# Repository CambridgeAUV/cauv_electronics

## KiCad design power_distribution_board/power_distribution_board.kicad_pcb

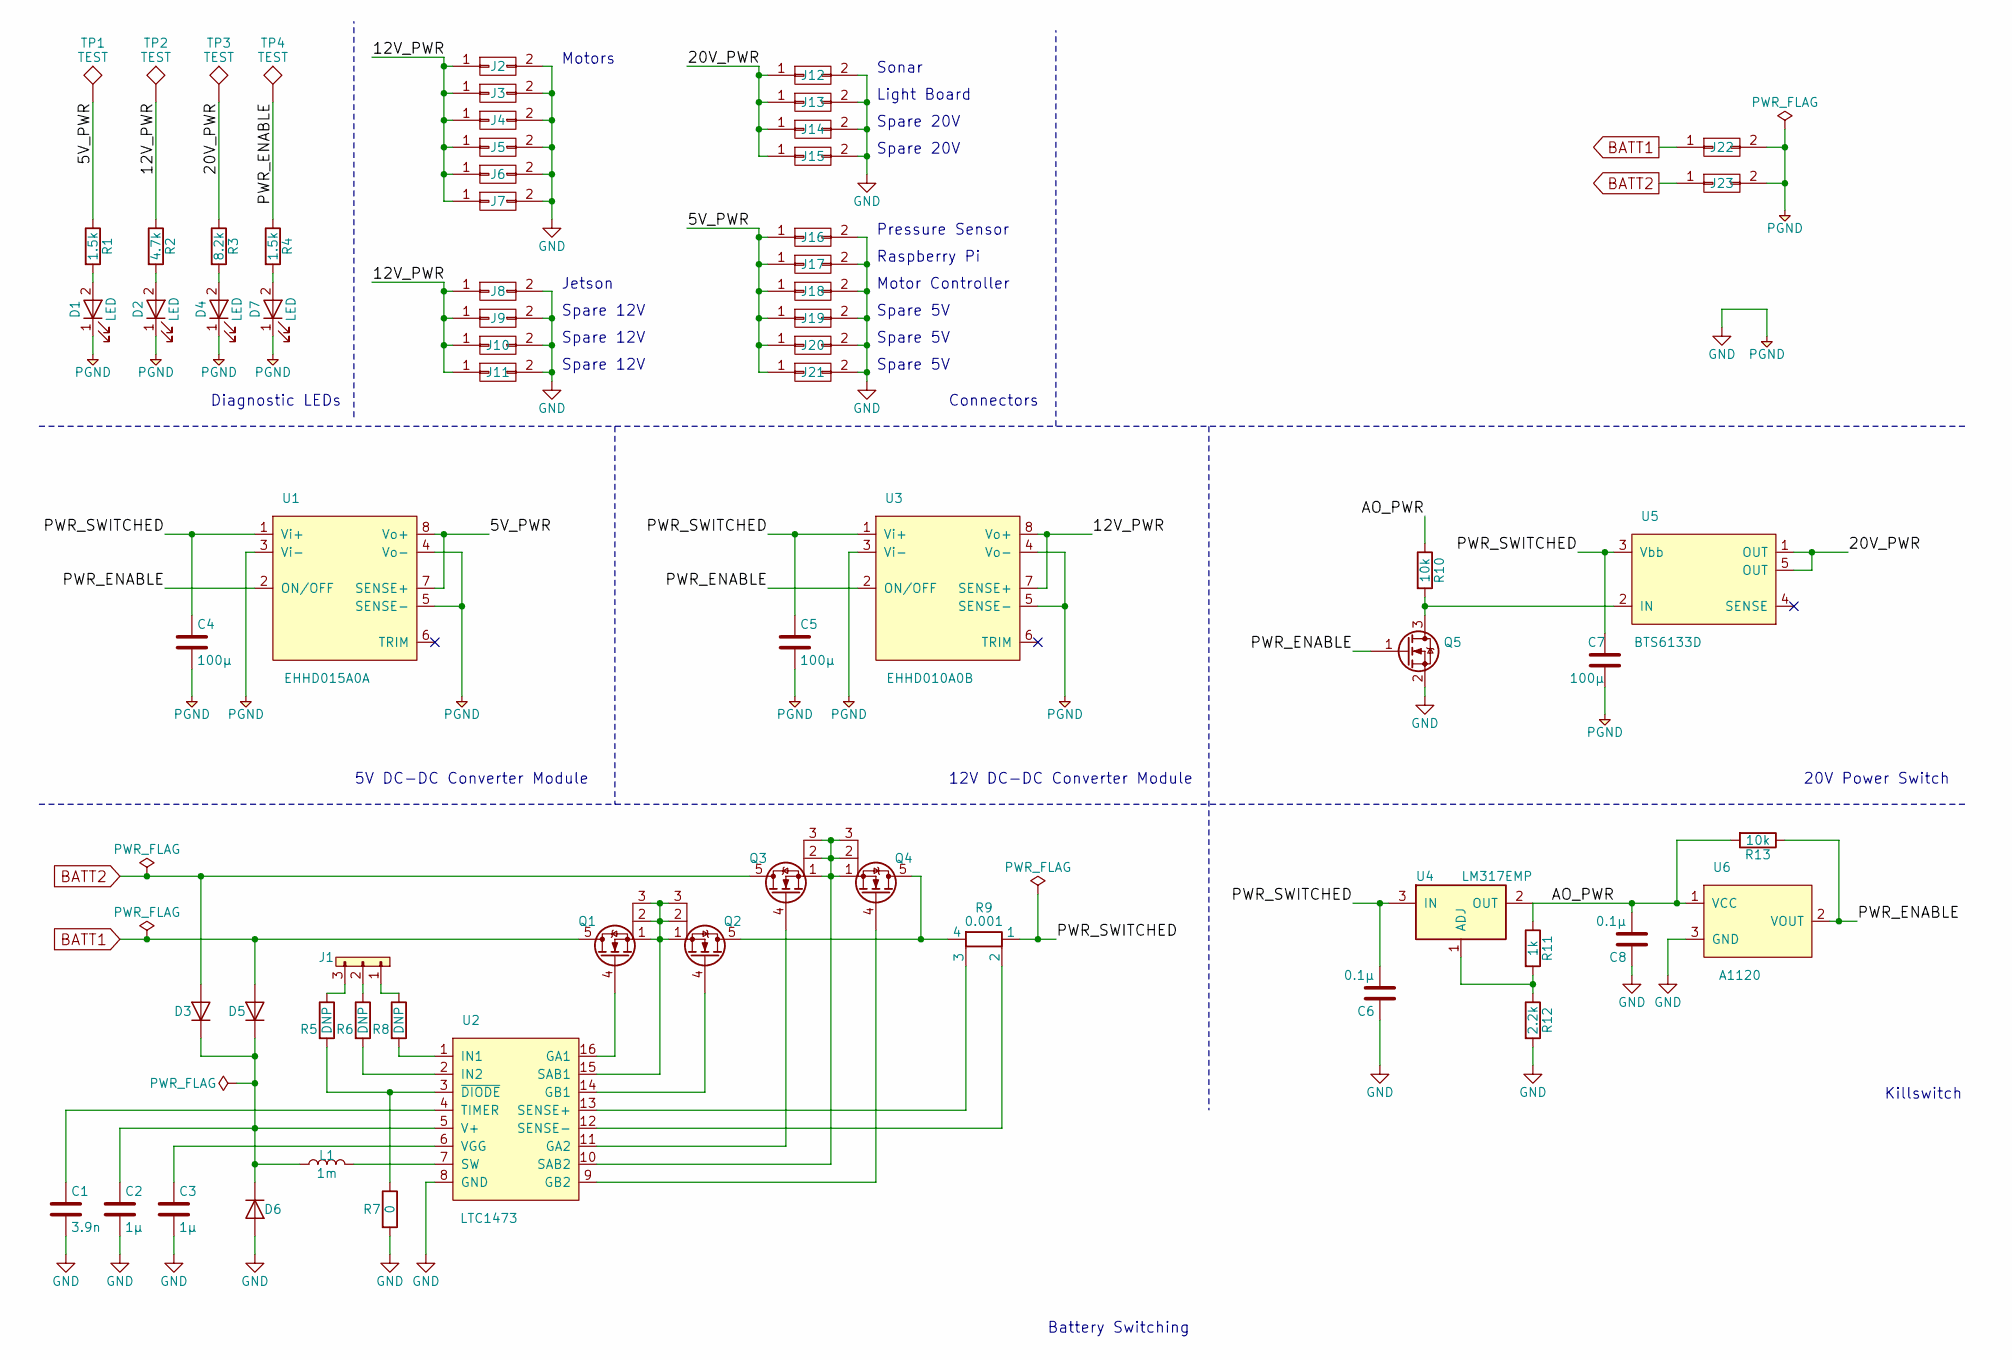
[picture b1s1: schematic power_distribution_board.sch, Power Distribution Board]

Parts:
C1: 3.9n; C_0603
C2, C3: 1μ; C_0603
C4, C5, C7: 100μ; C_1210
C6, C8: 0.1μ; C_0603
D1, D2, D4, D7: LED; LED_0805
D3, D5, D6: D; D_SMA
J1: CONN_01x03; Molex_KK-6410-03_03x2.54mm_Straight
J2, J3, J4, J5, J6, J7, J8, J9, J10, J11, J12, J13, J14, J15, J16, J17, J18, J19, J20, J21, J22, J23: CONN_02X01; Molex_MiniFit-JR-5556-02A_2x01x4.20mm_Straight
L1: 1m; L_1812
Q1, Q2, Q3, Q4: NMOS_SSSGD; SOT-669_LFPAK
Q5: Q_NMOS_GSD; SOT-23
R1, R4: 1.5k; R_0603
R2: 4.7k; R_0603
R3: 8.2k; R_0603
R5, R6, R8: DNP; R_0603
R7: 0; R_0603
R9: 0.001; WSLP2726
R10, R13: 10k; R_0603
R11: 1k; R_0603
R12: 2.2k; R_0603
TP1, TP2, TP3, TP4: TEST; TESTPAD
U1: EHHD015A0A
U2: LTC1473; SSOP-16_3.9x4.9mm_Pitch0.635mm
U3: EHHD010A0B; EHHD015A0A
U4: LM317EMP; SOT-223
U5: BTS6133D; TO-252-5_TabPin3
U6: A1120; Molex_KK-6410-03_03x2.54mm_Straight

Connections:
/5V_PWR: J16.1, J17.1, J18.1, J19.1, J20.1, J21.1, R1.1, TP1.1, U1.7 (SENSE+), U1.8 (Vo+)
/12V_PWR: J2.1, J3.1, J4.1, J5.1, J6.1, J7.1, J8.1, J9.1, J10.1, J11.1, R2.1, TP2.1, U3.7 (SENSE+), U3.8 (Vo+)
/20V_PWR: J12.1, J13.1, J14.1, J15.1, R3.1, TP3.1, U5.1 (OUT), U5.5 (OUT)
/AO_PWR: C8.2, R10.1, R11.1, R13.2, U4.2 (OUT), U6.1 (VCC)
/PWR_ENABLE: Q5.1 (G), R4.1, R13.1, TP4.1, U1.2 (ON/OFF), U3.2 (ON/OFF), U6.2 (VOUT)
/PWR_SWITCHED: C4.1, C5.1, C6.2, C7.1, R9.1, U1.1 (Vi+), U3.1 (Vi+), U4.3 (IN), U5.3 (Vbb)
BATT1: D5.2 (A), J22.1, Q1.5 (D)
BATT2: D3.2 (A), J23.1, Q3.5 (D)
GND: C1.2, C2.2, C3.2, C4.2, C5.2, C6.1, C7.2, C8.1, D1.1 (K), D2.1 (K), D4.1 (K), D6.2 (A), D7.1 (K), J2.2, J3.2, J4.2, J5.2, J6.2, J7.2, J8.2, J9.2, J10.2, J11.2, J12.2, J13.2, J14.2, J15.2, J16.2, J17.2, J18.2, J19.2, J20.2, J21.2, J22.2, J23.2, Q5.2 (S), R7.2, R12.2, U1.3 (Vi-), U1.4 (Vo-), U1.5 (SENSE-), U2.8 (GND), U3.3 (Vi-), U3.4 (Vo-), U3.5 (SENSE-), U6.3 (GND)
unnamed: C1.1, U2.4 (TIMER)
unnamed: C2.1, D3.1 (K), D5.1 (K), D6.1 (K), L1.1, U2.5 (V+)
unnamed: C3.1, U2.6 (VGG)
unnamed: D1.2 (A), R1.2
unnamed: D2.2 (A), R2.2
unnamed: D4.2 (A), R3.2
unnamed: D7.2 (A), R4.2
unnamed: J1.1, R8.1
unnamed: J1.2, R6.1
unnamed: J1.3, R5.1
unnamed: L1.2, U2.7 (SW)
unnamed: Q1.1 (S), Q1.2 (S), Q1.3 (S), Q2.1 (S), Q2.2 (S), Q2.3 (S), U2.15 (SAB1)
unnamed: Q1.4 (G), U2.16 (GA1)
unnamed: Q2.4 (G), U2.14 (GB1)
unnamed: Q2.5 (D), Q4.5 (D), R9.4
unnamed: Q3.1 (S), Q3.2 (S), Q3.3 (S), Q4.1 (S), Q4.2 (S), Q4.3 (S), U2.10 (SAB2)
unnamed: Q3.4 (G), U2.11 (GA2)
unnamed: Q4.4 (G), U2.9 (GB2)
unnamed: Q5.3 (D), R10.2, U5.2 (IN)
unnamed: R5.2, R7.1, U2.3 (~DIODE)
unnamed: R6.2, U2.2 (IN2)
unnamed: R8.2, U2.1 (IN1)
unnamed: R9.2, U2.12 (SENSE-)
unnamed: R9.3, U2.13 (SENSE+)
unnamed: R11.2, R12.1, U4.1 (ADJ)

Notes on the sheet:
Battery Switching
Killswitch
5V DC-DC Converter Module
12V DC-DC Converter Module
20V Power Switch
Diagnostic LEDs
Motors
Jetson
Spare 12V
Sonar
Light Board
Spare 20V
Pressure Sensor
Raspberry Pi
Motor Controller
Spare 5V
Connectors

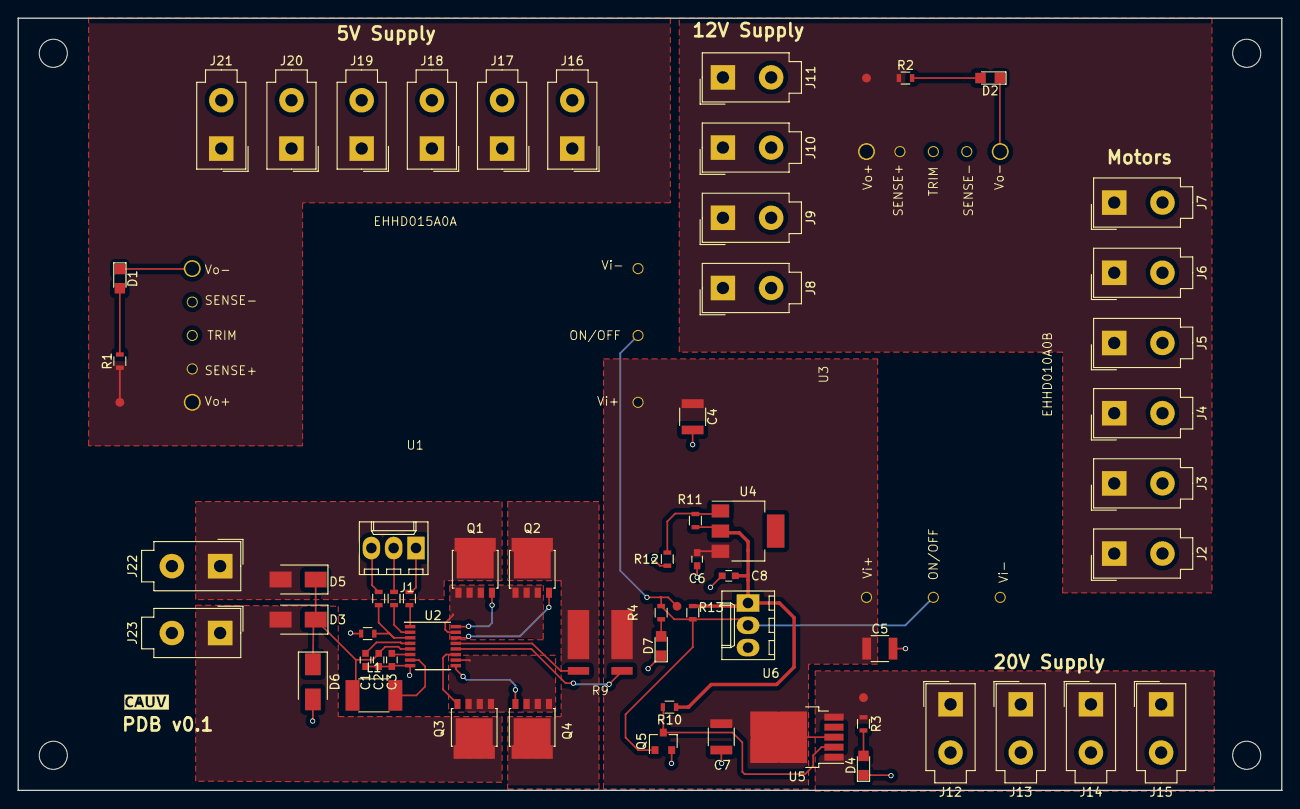
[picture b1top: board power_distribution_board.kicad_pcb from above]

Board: 2 copper layers, 144.0 x 88.0 mm, 67 parts (0 on the bottom side), 34 nets.

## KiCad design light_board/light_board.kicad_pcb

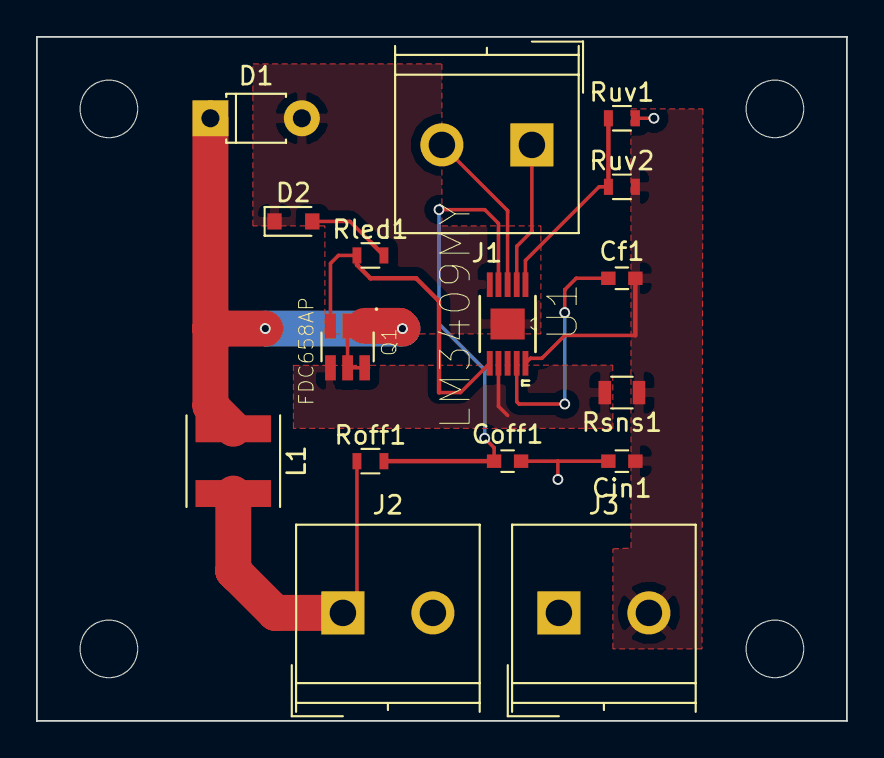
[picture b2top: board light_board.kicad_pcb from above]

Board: 2 copper layers, 45.0 x 38.0 mm, 16 parts (0 on the bottom side), 12 nets.

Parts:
Cf1: 1uF; C_0603
Cin1: 4u7F; C_0603
Coff1: 470pF; C_0603
D1: SCHOTTKY; D_T-1_P5.08mm_Horizontal
D2: Gate; D_0805
J1: PWM; TerminalBlock_Philmore_TB132_02x5mm_Straight
J2: Led; TerminalBlock_Philmore_TB132_02x5mm_Straight
J3: Power; TerminalBlock_Philmore_TB132_02x5mm_Straight
L1: 12.5uH; L_Taiyo-Yuden_MD-5050
Q1: FDC658AP; FDC658AP_FDC658AP
Rled1: 1kR; R_0603
Roff1: 12k; R_0603
Rsns1: 0.15R; R_0805
Ruv1: 6K49; R_0603
Ruv2: 73K2; R_0603
U1: LM3409MY; LM3409

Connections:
/COFF: Coff1.1, Roff1.2, U1.4
/CSN: Q1.4, Rsns1.2, U1.7
/CSP: Cf1.2, Cin1.1, J3.2, Rsns1.1, Ruv2.2, U1.8, U1.10
/LEDVcc: J2.1, L1.2, Roff1.1
/PGATE: Q1.3, Rled1.1, U1.6
/UVLO: Ruv1.1, Ruv2.1, U1.1
/diodeToLToPMOS: D1.1, L1.1, Q1.1, Q1.2, Q1.5, Q1.6
/inputSignal: J1.2, U1.3
/notUsed: J1.1, U1.2
GND: Cin1.2, Coff1.2, D1.2, D2.1, J2.2, J3.1, Ruv1.2, U1.5, U1.11
unnamed: Cf1.1, U1.9
unnamed: D2.2, Rled1.2

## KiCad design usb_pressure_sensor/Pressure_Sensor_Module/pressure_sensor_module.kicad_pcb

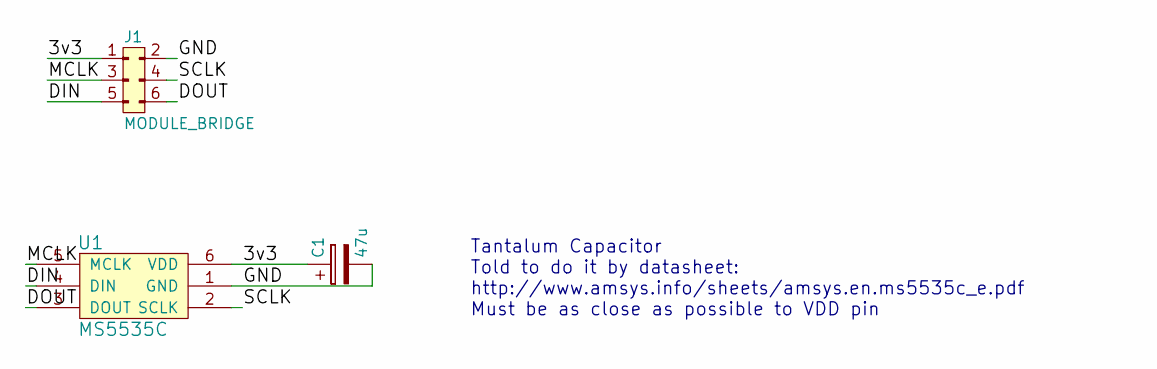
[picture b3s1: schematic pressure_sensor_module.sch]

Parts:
C1: 47u; CP_Tantalum_Case-C_EIA-6032-28_Reflow
J1: MODULE_BRIDGE; Socket_Strip_Straight_2x03_Pitch2.54mm
U1: MS5535C

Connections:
/3v3: C1.1, J1.1, U1.6 (VDD)
/DIN: J1.5, U1.4 (DIN)
/DOUT: J1.6, U1.3 (DOUT)
/GND: C1.2, J1.2, U1.1 (GND)
/MCLK: J1.3, U1.5 (MCLK)
/SCLK: J1.4, U1.2 (SCLK)

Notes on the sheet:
Tantalum Capacitor Told to do it by datasheet: http://www.amsys.info/sheets/amsys.en.ms5535c_e.pdf Must be as close as possible to VDD pin

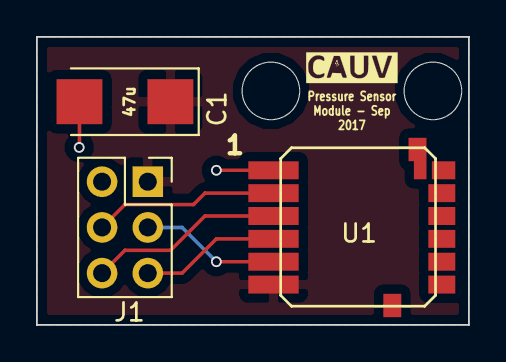
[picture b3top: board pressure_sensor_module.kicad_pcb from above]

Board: 2 copper layers, 24.0 x 16.0 mm, 3 parts (0 on the bottom side), 6 nets.

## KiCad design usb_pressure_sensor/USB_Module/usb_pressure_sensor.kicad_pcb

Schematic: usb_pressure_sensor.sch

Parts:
C1, C2: 1u; C_0603
C3, C4: 24p; C_0603
D1, D2: LED; LED_0805
IC1: STM32F042F6P6; TSSOP-20; Farnell 2469549
IC2: MCP1700; SOT-23; Farnell 1296592
J1: CONN_02x09; Pin_Header_Straight_2x09_Pitch2.54mm
J2: MODULE_BRIDGE; Socket_Strip_Straight_2x03_Pitch2.54mm
P1: SWD_TC; SWD_CONN
R1, R2: 22; R_Axial_DIN0207_L6.3mm_D2.5mm_P7.62mm_Horizontal
R3: 10k; R_0603
R4: 2.2M; R_0603
R5: 180k; R_0603
R6, R7: R; R_0805
U1: MICRO_USB; MICROUSB_MOLEX_47589-0001
U2: SN74LVC1GX04; SOT-23-6
U3: KSC341J:SWITCH; KSC431J_SWITCH
Y1: Crystal 32.768kHz; ABS07-32dot768kHz_Crystal

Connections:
/3v3: C2.1, IC1.5 (VDDA), IC1.16 (VDD), IC2.2 (VOUT), J1.1, J2.1, P1.1 (VDD), U2.5 (VCC), U3.3
/5v: C1.1, IC2.3 (VIN), R7.1, U1.1 (Vbus)
/DIN: IC1.13 (PA7), J1.17, J2.5
/DOUT: IC1.12 (PA6), J1.15, J2.6
/GND: C1.2, C2.2, C3.2, C4.2, D1.1 (K), D2.1 (K), IC1.15 (VSS), IC2.1 (GND), J1.2, J2.2, P1.5 (GND), R3.2, U1.5 (GND), U2.2 (GND)
/MCLK: J2.3, R4.1, R5.1, U2.4 (X2)
/NRST: IC1.4 (NRST), P1.3 (~RST)
/PA0: IC1.6 (PA0), J1.3, R6.2
/PA1: IC1.7 (PA1), J1.5
/PA2: IC1.8 (PA2), J1.7
/PA3: IC1.9 (PA3), J1.9
/PA4: IC1.10 (PA4), J1.11
/PB1: IC1.14 (PB1), J1.12
/PB8: IC1.1 (PB8/BOOT0), J1.14, R3.1, U3.2
/PF0: IC1.2 (PF0), J1.16
/PF1: IC1.3 (PF1), J1.18
/SCLK: IC1.11 (PA5), J1.13, J2.4
/SWDCLK: IC1.20 (PA14), J1.10, P1.4 (SWDCLK)
/SWDIO: IC1.19 (PA13), J1.8, P1.2 (SWDIO)
/USB_DM: IC1.17 (PA9/PA11), J1.4, R1.2
/USB_DP: IC1.18 (PA10/PA12), J1.6, R2.1
unnamed: C3.1, R4.2, U2.3 (X1), Y1.1
unnamed: C4.1, R5.2, Y1.2
unnamed: D1.2 (A), R6.1
unnamed: D2.2 (A), R7.2
unnamed: R1.1, U1.2 (D-)
unnamed: R2.2, U1.3 (D+)

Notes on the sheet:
Capacitor should be as close as possible to VOUT pin
Crystal Oscillator
Crystal Oscillator design process: For the values used http://www.ti.com/lit/an/szza043/szza043.pdf page 13 180k should be approx equal to capacitave reactance of one of the capacitors connected to gound. Used 1/j*2pi*f*C where f is the resonant freq of the crystal. 2.2M should be between 1M and 10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
Power Supply
USB Interface
Serial Wire Debugging
Module Bridge
MCU
Chose 22ohm because: http://www.eevblog.com/forum/projects/why-usb-data-series-resistors/
I'm using the SPI pins even though the pressure sesnsor doesn't say it uses SPI but it should be the same concepts right? Even if we can't hack SPI into working these pins are still general purpose IO so i think it's ok?
MCU PINOUT
We should provide a pinout header so that we could reuse this board for other purposes in the future. If these headers are not needed, they can simply be left unsoldered. This will, however, make the board slightly larger due to the length of the 2x9 header and the more complex routes
LED type we already have: LGR971 green
LED Design Process: PA0 is a TTa pin (from datasheet) which is 3.3V. LED is type LGR971 which has forward voltage drop of 2.2V LED requires 25mA so resistor value is (1.1)/0.025 = 44 ohms Nearest lower value we have is 39 ohm 0603
[Comment now obsolete] For the LED, just copied this http://www.instructables.com/id/Simple-USB-Tester/ I really don't know how to correctly choose the resistor value since I don't know how much the Data pins can sink so i'll just stick with the instrucbles value of 1k
I'm also not sure whether it should go before or after the termination resistors

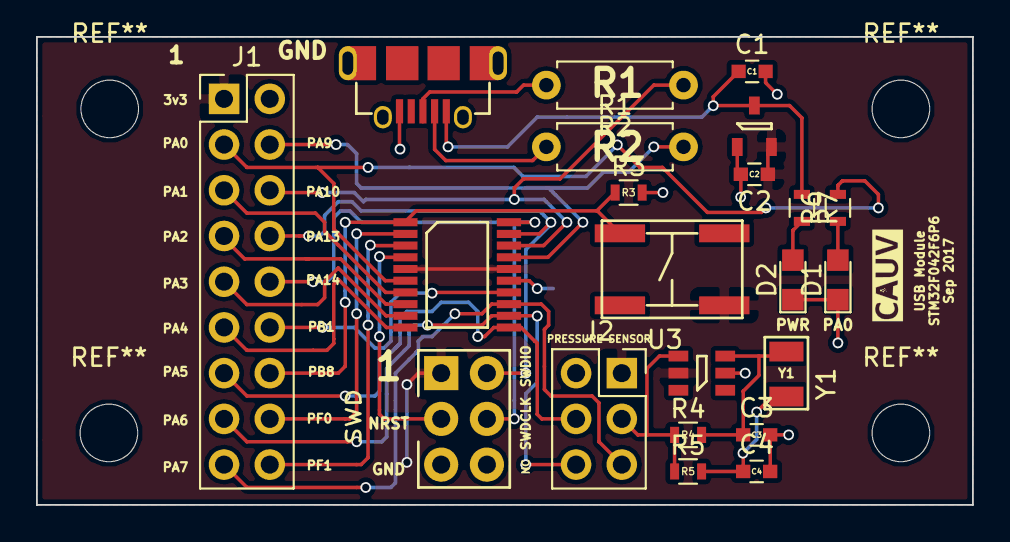
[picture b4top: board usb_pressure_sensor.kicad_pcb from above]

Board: 2 copper layers, 52.0 x 26.0 mm, 22 parts (0 on the bottom side), 27 nets.

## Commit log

2017-07-16 Changed 0805 capacitors and resistors to 0603
    Polarised capacitors and through hole resistors unchanged
2017-07-16 Actually made the changes on the pcb
2017-07-18 Made sure to commit all the resistor changes to the footprint that we already own
2017-07-29 add empty power distribution project
2017-07-29 fixup! add cauv and agg component libraries
2017-07-29 add cauv and agg component libraries
2017-07-29 update cauv_lib with schematic symbols
2017-07-29 add battery switching circuit
2017-07-29 add header to debug battery switch control
2017-07-29 add hall effect killswitch
2017-07-29 add label to battery switch output
2017-07-30 add 5v converter module
2017-07-30 add EHHD010A0B to cauv_lib
2017-07-30 add 12v converter module
2017-07-30 add power supply (via lm317) to killswitch
2017-07-30 fixup! add power supply (via lm317) to killswitch
2017-07-30 add 20V power switch
2017-07-30 add diagnostic LEDs
2017-07-30 add connectors
2017-07-30 update component values for battery switching
2017-07-30 annotate and fix warnings/errors
    Added:
    - Power flags
    - Battery connectors
    Fixed:
    - Incorrect net names
    'Fixed':
2017-08-05 add custom footprints
2017-08-05 assign footprints
2017-08-12 initial grouping of related components on pcb
2017-08-12 initial attempt at routing for LTC1743
2017-08-12 minor improvements to LTC1473 routing
2017-08-12 initial routing of killswitch subcircuit
2017-08-12 Update BTS6133D to have the correct footprint
2017-08-13 improvements to layout of killswitch subcircuit
2017-08-16 Schematics for usb pressure sensor module(s)
    Also renamed a file in cauv_lib/footprints.pretty that had a space in it which meant it caused problems for me
2017-08-18 Added PCB for pressure module
2017-08-19 a few more things routed
2017-08-20 Started update to different pressure sensor module
2017-08-20 First iteration with new pressure sensor
2017-08-21 added pin header to all pins on the MCU
2017-08-23 PCB design with new pressure sensor and some footprints
2017-08-26 Added comments to light board
2017-08-27 Routed pin header and swd connector
2017-08-27 Finished usb_module routing
2017-09-07 added cuts and drills + logos into the PCBs
2017-09-08 finish pdb
2017-09-09 Added LEDs to schematic
    Removed cut since the cut needs to be aligned with the usb connector line so the sub connector hangs over the edge of the pcb
2017-09-12 added LEDs
2017-09-22 added mounting holes and changed light board footprints
2017-09-24 Moved usb connector
    The connector has a line on the footprint which corresponds to the edge of the pcb so I moved it upwards such that this line becomes coincident with the pcb cut edge
2017-09-24 Moved usb connector
    Moved connector upwards so that the line on the footprint which represents the pcb edge lines up with the actual pcb edge
2017-09-24 Changed PA0 via location
    The previous location cut off a section of the 3v3 plane from the rest of the plane
2017-09-24 changed orientation of pmos and the wiring of R3
2017-09-25 removed unnecessary via
2017-09-25 add order sheet to power distribution board
2017-09-26 changed values and names in eeschema file
2017-09-27 finished labeling components and lines. Still need to complete footprints for light board
2017-09-28 finished wiring pcb
2017-09-28 light_board finished
2017-09-30 changed footprints of resistor and diode
2017-09-30 change inductor footprint; update order sheet
2017-10-01 Added pressure sensor gerber&drills
2017-10-01 light board finished - added ground plane and thick tracks
2017-10-01 final modifications
2017-10-01 regenerated gerber for pdb
